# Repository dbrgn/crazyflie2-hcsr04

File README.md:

# Crazyflie 2.0 HC-SR04 Ultrasonic Expansion

This adds support for a cheap ultrasonic sensor (HC-SR04) to the Crazyflie 2.0.

## Parts

- 1x [HC-SR04](http://www.micropik.com/PDF/HCSR04.pdf)
- 1x [TI REG71050DDCT](http://www.ti.com/litv/sbas221g)
- 1x [Maxim DS28E05](http://www.mouser.com/ds/2/256/DS28E05-473078.pdf)
- 2x [Taiyo Yuden 2.2 uF EMK316BJ225KL-T](http://www.yuden.co.jp/eu/product/category/capacitor/EMK316BJ225KL-T.html)
- 1x [Taiyo Yuden 0.22 uF LMK107B7224KA-T](http://www.yuden.co.jp/eu/product/category/capacitor/LMK107B7224KA-T.html)

## GPIO Ports

The HC-SR04 expansion board uses the following GPIO ports:

- `IO_1 / PB8`: HC-SR04 Trigger
- `IO_2 / PB5`: HC-SR04 Echo
- `IO_4 / PC12`: REG71050 Enable

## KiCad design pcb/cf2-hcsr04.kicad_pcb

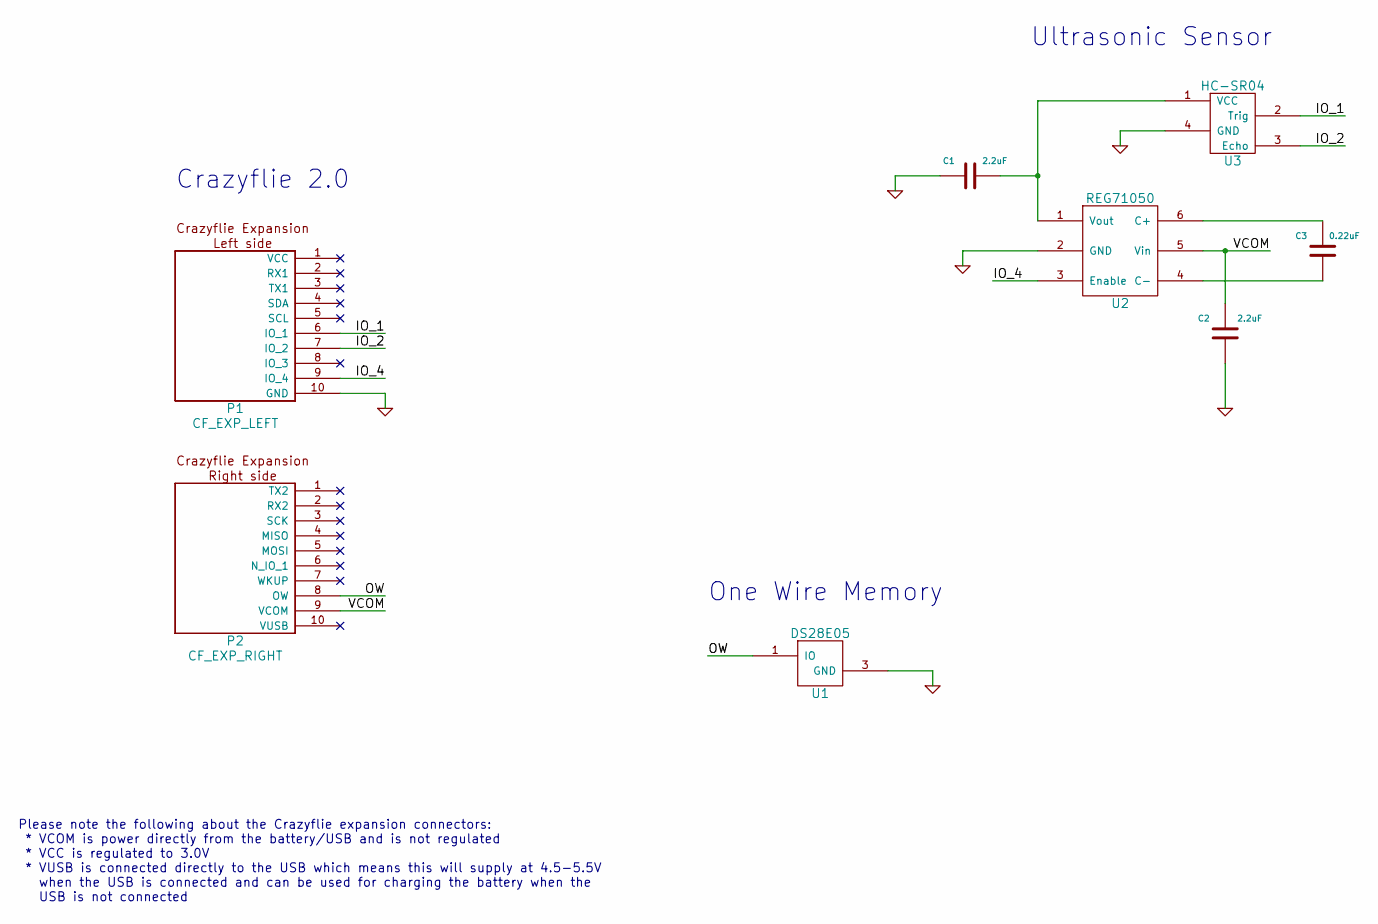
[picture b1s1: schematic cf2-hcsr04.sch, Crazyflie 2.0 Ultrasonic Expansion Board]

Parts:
C1, C2: 2.2uF
C3: 0.22uF
P1: CF_EXP_LEFT
P2: CF_EXP_RIGHT
U1: DS28E05
U2: REG71050
U3: HC-SR04

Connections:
/IO_1: P1.6 (IO_1), U3.2 (Trig)
/IO_2: P1.7 (IO_2), U3.3 (Echo)
/IO_4: P1.9 (IO_4), U2.3 (Enable)
/OW: P2.8 (OW), U1.1 (IO)
/VCOM: C2.2, P2.9 (VCOM), U2.5 (Vin)
GND: C1.1, C2.1, P1.10 (GND), U1.3 (GND), U2.2 (GND), U3.4 (GND)
unnamed: C3.2, U2.6 (C+)
unnamed: C1.2, U2.1 (Vout), U3.1 (VCC)
unnamed: C3.1, U2.4 (C-)

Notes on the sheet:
Please note the following about the Crazyflie expansion connectors: * VCOM is power directly from the battery/USB and is not regulated * VCC is regulated to 3.0V * VUSB is connected directly to the USB which means this will supply at 4.5-5.5V when the USB is connected and can be used for charging t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
Ultrasonic Sensor
One Wire Memory
Crazyflie 2.0

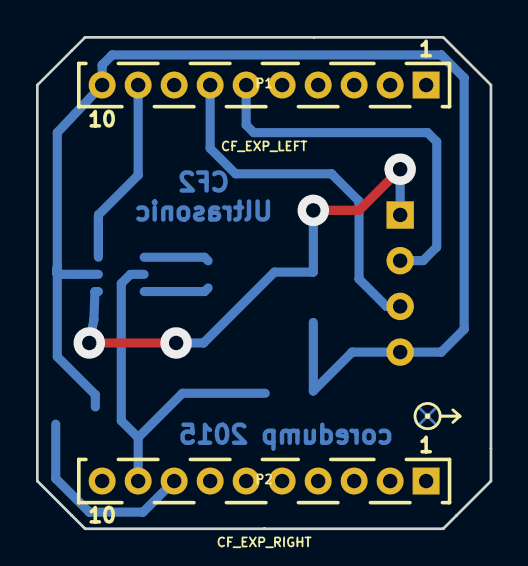
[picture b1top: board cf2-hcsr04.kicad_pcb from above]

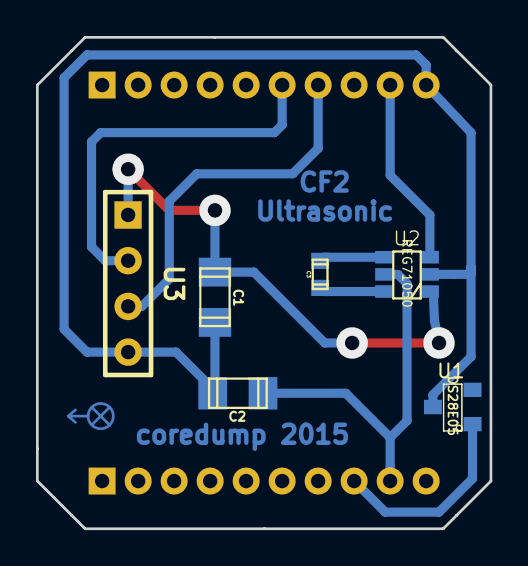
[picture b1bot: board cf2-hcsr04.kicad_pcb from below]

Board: 2 copper layers, 25.2 x 27.3 mm, 9 parts (6 on the bottom side), 9 nets.

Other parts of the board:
EXP_ORIENTATION: VAL**; EXP_ORIENTATION_B_MASK

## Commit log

2015-01-27 Initial version (schema)
2015-01-27 Added README, updated netlist
2015-02-02 Started work on footprint
2015-02-02 First pcb draft
2015-02-02 Improved thickness of vias and other connections
2015-02-02 Link to HCSR04 datasheet
2015-02-03 Added side information and text to footprint (fixes #1)
2015-02-09 Removed acute angle
2015-02-10 Exported current version as svg/pdf
2015-02-13 Unified connector footprints
2015-02-13 Increased clearance between some vias and traces
2015-02-13 Exported current version of board
2015-04-05 Added pictures
2015-04-05 Added schema PDF
2015-04-05 Added GPIO documentation to README
2015-04-05 Updated GPIO docs with real port IDs

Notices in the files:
pcb/cf2-hcsr04.kicad_pcb:
Licensed under CC-BY 4.0
